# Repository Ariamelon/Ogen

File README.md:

# Ogen
A PMW3360 breakout board. Works with up to 5.5V VCC and logic.

## Disclaimer
This board is licensed under CERN-OHL-S-2.0.

 ## Changelog
 * 22/10/2024: License updated to CERN-OHL-S-2.0.
 * 14/10/2023: V1.5 update. Changed LDO to XC6206P202MR. Unified libraries with master library.
 * 18/09/2023: Updated to V1.4. Fixed .gitignore file. Changed LDO capacitors to 4u7 to match the one used in the PMW3360.
 * 04/08/2023: Updated to V1.3. Changed all parts back to 0603. Stitched ground planes together. Removed MISO pullup jumper (MISO is pulled up by default now). Added metadata to schematic and PCB file. Changed location of production files for easier access. Changed default to Ogen Lite.
 * 29/03/2023: Changed logo.
 * 21/03/2023: Update to V1.2. Changed parts for smaller ones. Set up for JLC assembly.
 * 23/06/2022: Update to V1.1. Changed the 5 1-bit shift registers to 3 2-bit ones. Slightly shrunk board. New logo (very important).
 * 04/10/2020: Fixed major flaw in PMW3360 footprint.
 * 30/09/2020: Initial commit.

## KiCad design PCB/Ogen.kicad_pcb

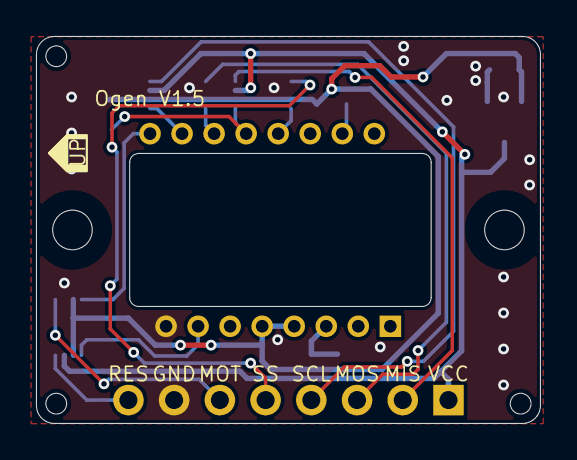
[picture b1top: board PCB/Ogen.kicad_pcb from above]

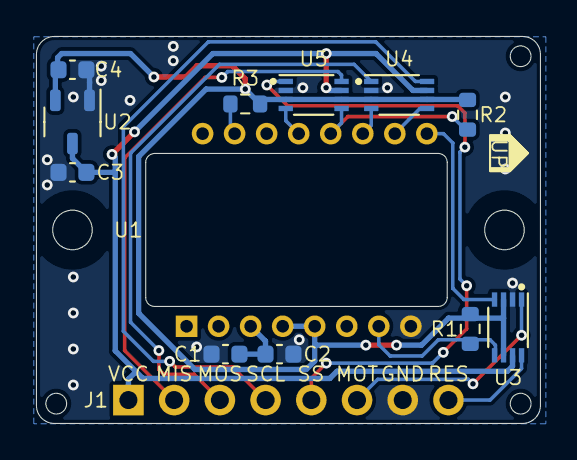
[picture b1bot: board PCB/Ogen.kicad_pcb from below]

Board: 2 copper layers, 28.0 x 21.5 mm, 19 parts (15 on the bottom side), 17 nets.

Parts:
A1: Art; Ariamelon_Logo-CU
C1, C3, C4: 4u7; C_0603_1608Metric
C2: 100n; C_0603_1608Metric
H1, H2: M2; MountingHole_2.2mm_M2
H3, H4, H5: Tooling Hole; JLC Tooling Hole
J1: Input; PinHeader_1x08_P2.54mm_Vertical
R1, R2: 10k; R_0603_1608Metric
R3: 39; R_0603_1608Metric
U1: PMW3360DM-T2QU_1; IC_PMW3360DM-T2QU
U2: XC6206P202MR; SOT-23-3
U3, U4, U5: TXS0102DCU; VSSOP-8_2.3x2mm_P0.5mm

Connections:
+2V: C4.1, R1.2, R2.1, R3.2, U1.4 (VDD), U1.5 (VDDIO), U2.2 (VO), U3.3 (VCCA), U3.6 (OE), U4.3 (VCCA), U4.6 (OE), U5.3 (VCCA), U5.6 (OE)
GND: C1.2, C2.1, C3.2, C4.2, J1.7, U1.8 (GND), U2.1 (GND), U3.2 (GND), U4.2 (GND), U5.2 (GND)
MISO: R2.2, U1.12 (MISO), U5.5 (A1)
MISO-H: J1.2, U5.8 (B1)
MOSI: U1.11 (MOSI), U4.4 (A2)
MOSI-H: J1.3, U4.1 (B2)
MOT: U1.9 (MOTION), U3.4 (A2)
MOT-H: J1.6, U3.1 (B2)
NRESET: R1.1, U1.7 (NRESET), U3.5 (A1)
NRESET-H: J1.8, U3.8 (B1)
unnamed: R3.1, U1.15 (LED_P)
unnamed: C1.1, C2.2, U1.3 (VDDPIX)
SCLK: U1.10 (SCLK), U4.5 (A1)
SCLK-H: J1.4, U4.8 (B1)
SS: U1.13 (NCS), U5.4 (A2)
SS-H: J1.5, U5.1 (B2)
VCC: C3.1, J1.1, U2.3 (VI), U3.7 (VCCB), U4.7 (VCCB), U5.7 (VCCB)

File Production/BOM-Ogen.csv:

Comment,Designator,Footprint,LCSC
100n,C2,C_0603_1608Metric,C14663
4u7,"C1,C3,C4",C_0603_1608Metric,C19666
39,R3,R_0603_1608Metric,C25236
10k,"R1,R2",R_0603_1608Metric,C25804
XC6206P202MR,U2,SOT-23-3,C2891260
TXS0102DCU,"U3,U4,U5",VSSOP-8_2.3x2mm_P0.5mm,C53434
PMW3360DM-T2QU_1,U1,IC_PMW3360DM-T2QU,

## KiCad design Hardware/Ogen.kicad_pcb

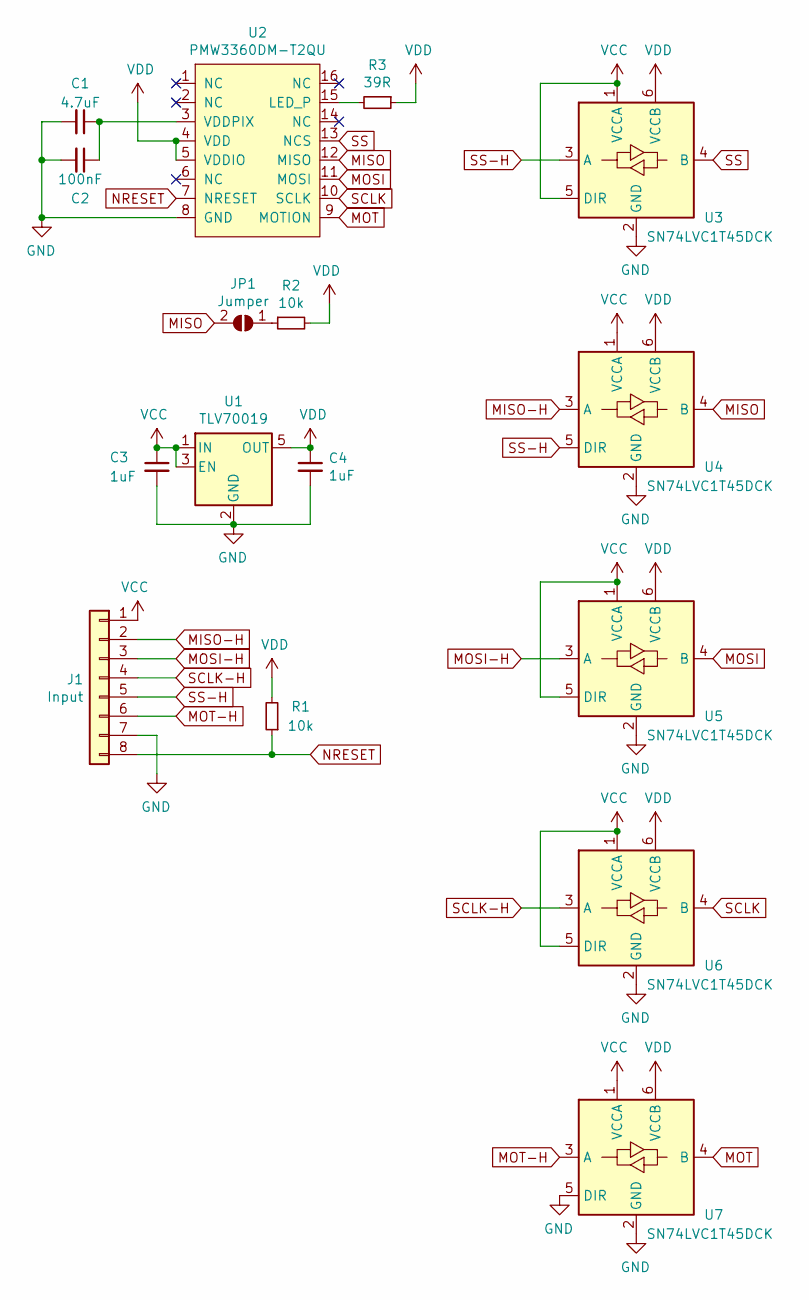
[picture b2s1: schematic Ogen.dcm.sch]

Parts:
C1: 4.7uF; C_0603_1608Metric
C2: 100nF; C_0603_1608Metric
C3, C4: 1uF; C_0603_1608Metric
J1: Input; PinHeader_1x08_P2.54mm_Vertical
JP1: Jumper; SolderJumper-2_P1.3mm_Open_Pad1.0x1.5mm
R1, R2: 10k; R_0603_1608Metric
R3: 39R; R_0603_1608Metric
U1: TLV70019; SOT-23-5
U2: PMW3360DM-T2QU
U3, U4, U5, U6, U7: SN74LVC1T45DCK; SOT-363_SC-70-6

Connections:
GND: C1.2, C2.2, C3.2, C4.2, J1.7, U1.2 (GND), U2.8 (GND), U3.2 (GND), U4.2 (GND), U5.2 (GND), U6.2 (GND), U7.2 (GND), U7.5 (DIR)
MISO: JP1.2 (B), U2.12 (MISO), U4.4 (B)
MISO-H: J1.2, U4.3 (A)
MOSI: U2.11 (MOSI), U5.4 (B)
MOSI-H: J1.3, U5.3 (A)
MOT: U2.9 (MOTION), U7.4 (B)
MOT-H: J1.6, U7.3 (A)
NRESET: J1.8, R1.1, U2.7 (NRESET)
unnamed: C1.1, C2.1, U2.3 (VDDPIX)
unnamed: JP1.1 (A), R2.1
unnamed: R3.2, U2.15 (LED_P)
SCLK: U2.10 (SCLK), U6.4 (B)
SCLK-H: J1.4, U6.3 (A)
SS: U2.13 (NCS), U3.4 (B)
SS-H: J1.5, U3.3 (A), U4.5 (DIR)
VCC: C3.1, J1.1, U1.1 (IN), U1.3 (EN), U3.1 (VCCA), U3.5 (DIR), U4.1 (VCCA), U5.1 (VCCA), U5.5 (DIR), U6.1 (VCCA), U6.5 (DIR), U7.1 (VCCA)
VDD: C4.1, R1.2, R2.2, R3.1, U1.5 (OUT), U2.4 (VDD), U2.5 (VDDIO), U3.6 (VCCB), U4.6 (VCCB), U5.6 (VCCB), U6.6 (VCCB), U7.6 (VCCB)

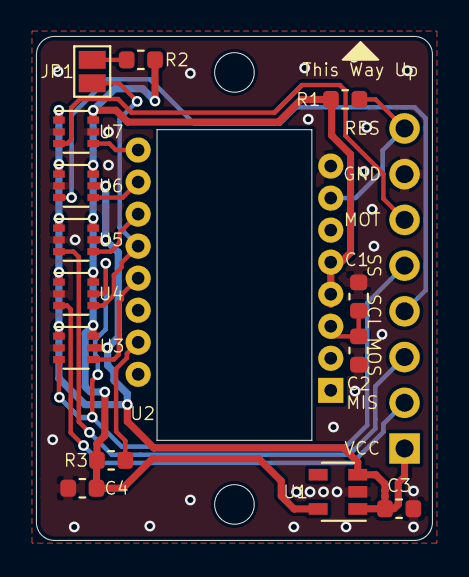
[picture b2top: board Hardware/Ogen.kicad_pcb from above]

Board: 2 copper layers, 22.0 x 28.0 mm, 16 parts (0 on the bottom side), 17 nets.

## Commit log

2020-09-29 Added readme
2020-09-29 Fixed traces
    Some traces weren't the right width so I fixed that. ALso did some minor rerouting.
2020-09-30 Update LICENSE
2020-10-01 Added images and updated readme
2020-10-04 Fixed major flaw in PMW3360 footprint
2020-10-24 Updated silk, better render
2020-10-24 Fixed image link oops
2022-06-23 Updated to V1.1
2023-03-21 V1.2 update.
2023-03-21 V1.0 Lite initial commit.
2023-03-29 Update README.md f
2023-03-29 Changed logo.
2023-08-04 04/08/2023 update
    Updated to V1.3. Changed all parts back to 0603. Stitched ground planes together. Removed MISO pullup jumper (MISO is pulled up by default now). Added metadata to schematic and PCB file. Changed loca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
2023-08-04 04/08/2023 update
    Updated to V1.1. Changed capacitors and resistors to 0603. Stitched ground planes together. Removed MISO pullup jumper (MISO is pulled up by default now). Added metadata to schematic and PCB file. Ch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
2023-09-18 18/09/2023 update
    Fixed .gitignore file. Changed LDO capacitors to 4u7 to match the one used in the PMW3360.
2023-09-18 18/09/2023 update
    Updated to V1.4. Fixed .gitignore file. Changed LDO capacitors to 4u7 to match the one used in the PMW3360.
2023-10-14 V1.3 update
    Changed LDO to XC6206P202MR.
2023-10-14 V1.5 update
    Changed LDO to XC6206P202MR. Unified libraries with master library.
2024-10-22 License updated to CERN-OHL-S-2.0.

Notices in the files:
PCB/Ogen.kicad_pcb:
Licensed under CC BY 4.0.
